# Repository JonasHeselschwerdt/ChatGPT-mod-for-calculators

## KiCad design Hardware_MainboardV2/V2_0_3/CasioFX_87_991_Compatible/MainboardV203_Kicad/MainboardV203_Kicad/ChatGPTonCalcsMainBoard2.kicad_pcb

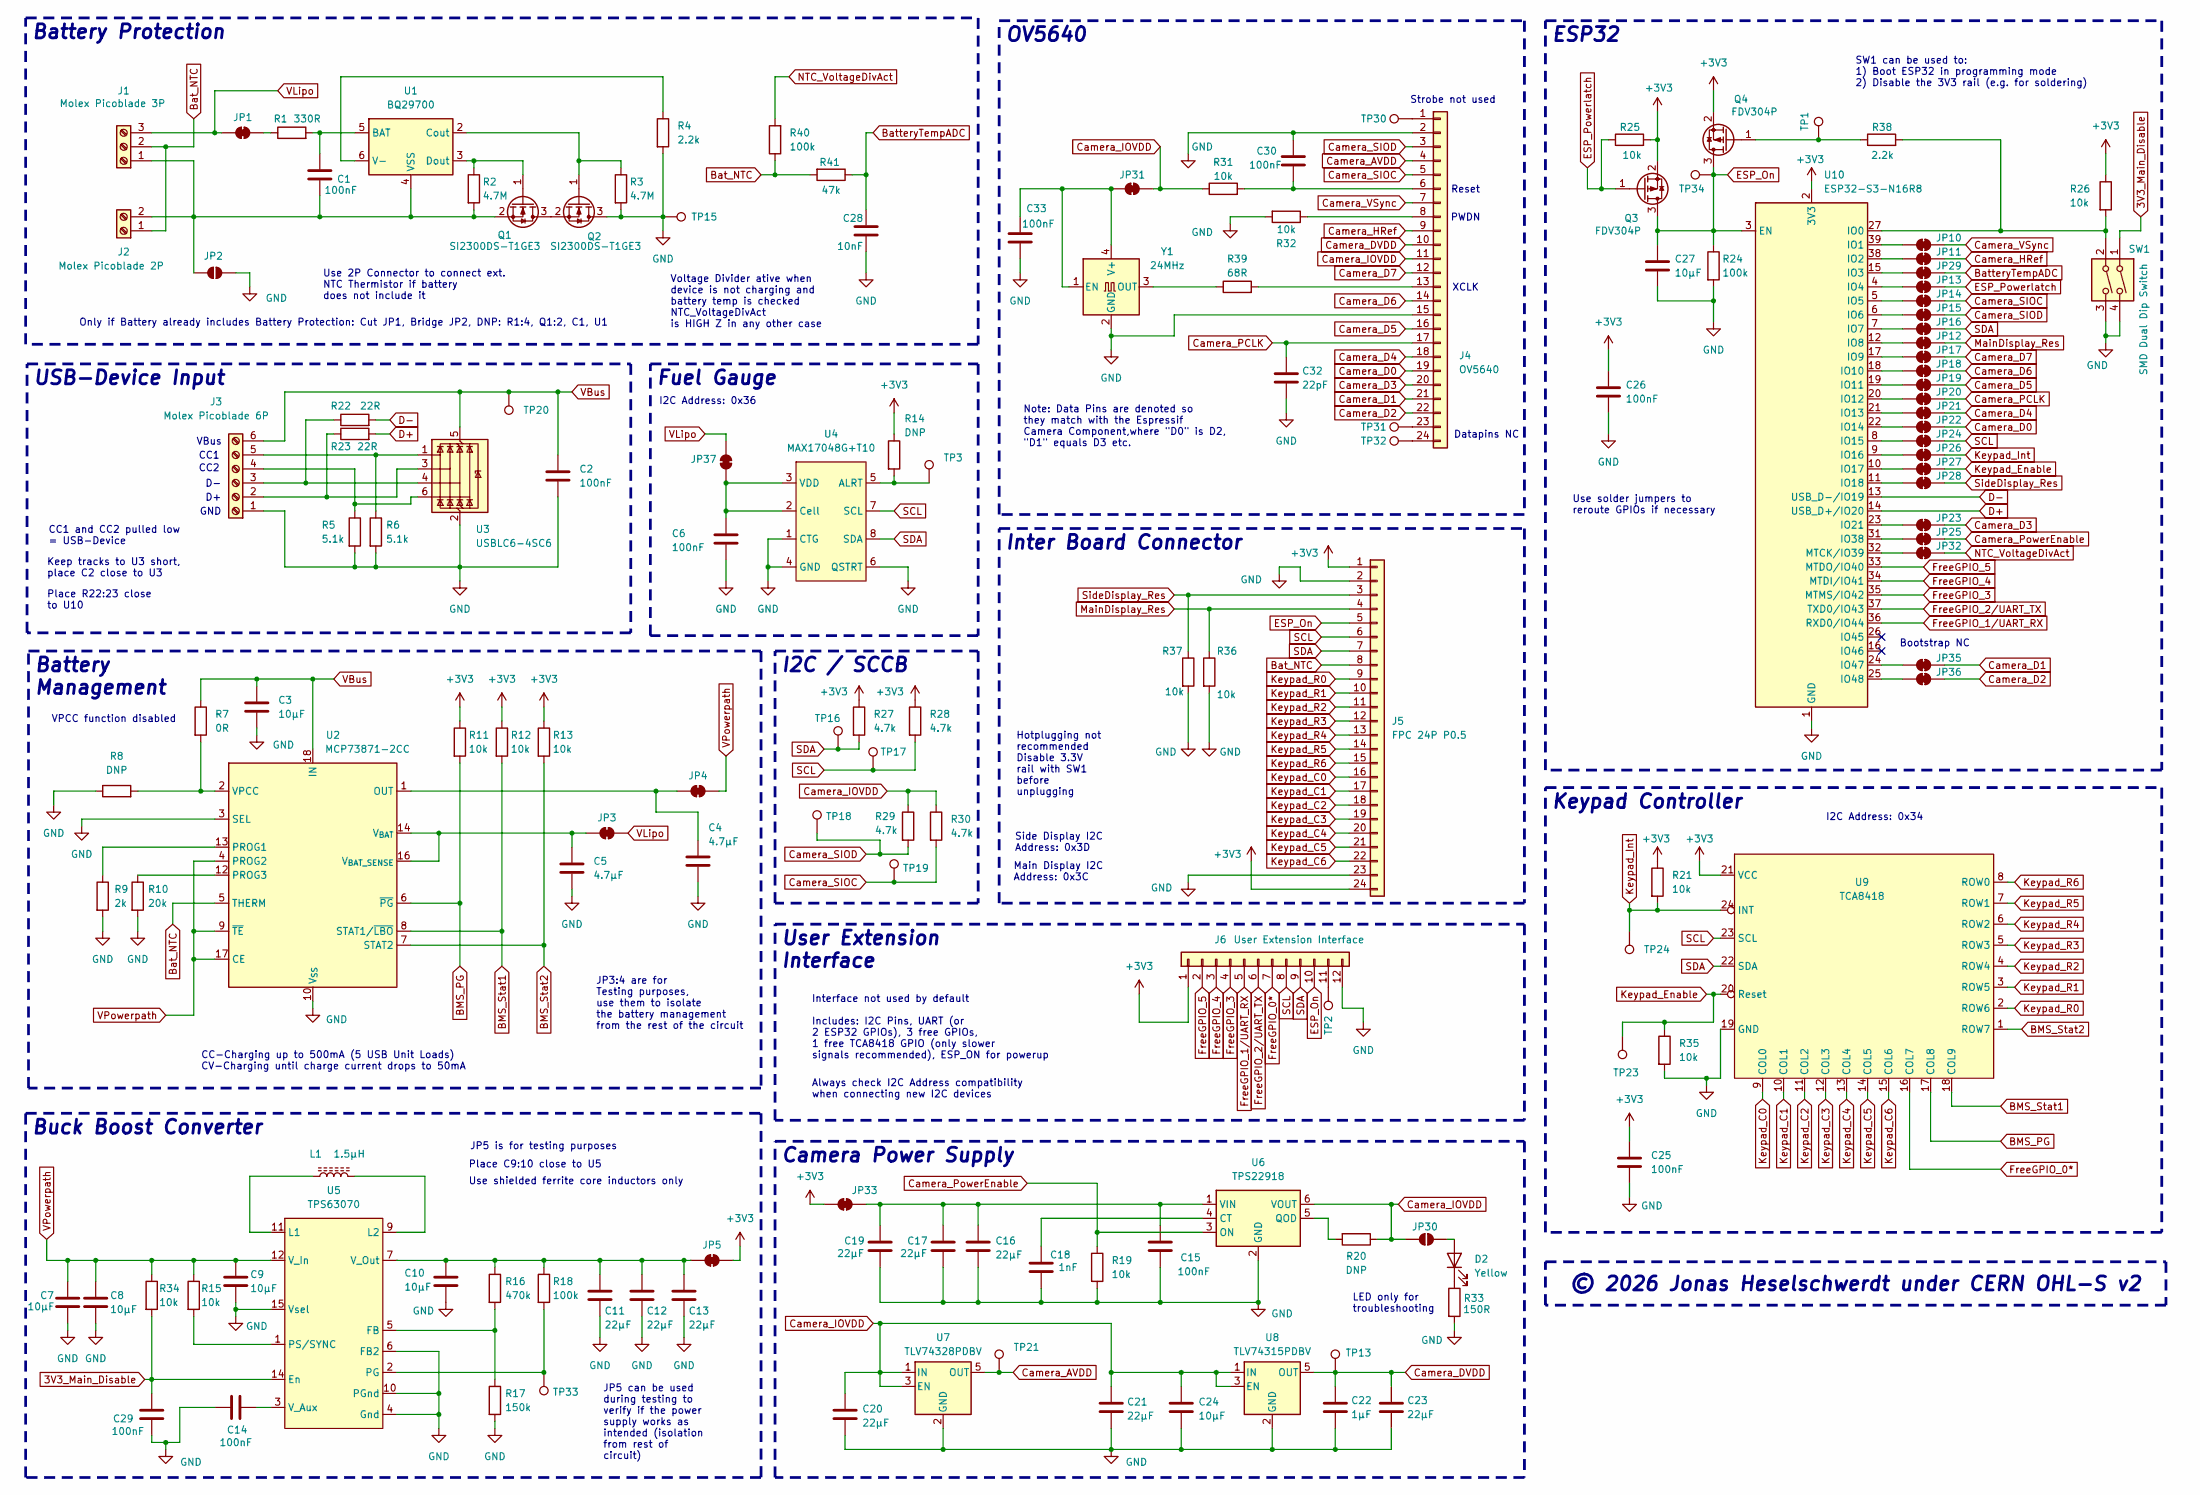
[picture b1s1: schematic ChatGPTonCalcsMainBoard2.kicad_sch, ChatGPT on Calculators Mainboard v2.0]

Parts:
C1, C2, C6, C14, C15, C25, C26, C29, C30, C33: 100nF; C_0603_1608Metric
C3, C7, C8, C9, C10, C24, C27: 10µF; C_0603_1608Metric
C4, C5: 4.7µF; C_0603_1608Metric
C11, C12, C13, C16, C17, C19, C20, C21, C23: 22µF; C_0603_1608Metric
C18: 1nF; C_0603_1608Metric
C22: 1µF; C_0603_1608Metric
C28: 10nF; C_0603_1608Metric
C32: 22pF; C_0603_1608Metric
D2: Yellow; LED_0603_1608Metric
J1: Molex Picoblade 3P; Molex_PicoBlade_53261-0371_1x03-1MP_P1.25mm_Horizontal
J2: Molex Picoblade 2P; Molex_PicoBlade_53261-0271_1x02-1MP_P1.25mm_Horizontal
J3: Molex Picoblade 6P; Molex_PicoBlade_53261-0671_1x06-1MP_P1.25mm_Horizontal
J4: OV5640; 24Pin_FPC_P0.5_RecommendedLayout
J5: FPC 24P P0.5; 24Pin_FPC_P0.5_RecommendedLayout
J6: User Extension Interface; Calc_ExtensionInterfaceV202
JP1, JP3, JP4, JP5, JP10, JP11, JP12, JP13, JP14, JP15, JP16, JP17, JP18, JP19, JP20, JP21, JP22, JP23, JP24, JP25, JP26, JP27, JP28, JP29, JP31, JP32, JP33, JP35, JP36, JP37: SolderJumper_2_Bridged; SolderJumper-2_P1.3mm_Bridged_RoundedPad1.0x1.5mm
JP2, JP30: SolderJumper_2_Open; SolderJumper-2_P1.3mm_Open_RoundedPad1.0x1.5mm
L1: 1.5µH; SPM5030VT-1R5M-D
Q1, Q2: SI2300DS-T1GE3; TSOT-23
Q3, Q4: FDV304P; TSOT-23
R1: 330R; R_0603_1608Metric
R2, R3: 4.7M; R_0603_1608Metric
R4, R38: 2.2k; R_0603_1608Metric
R5, R6: 5.1k; R_0603_1608Metric
R7: 0R; R_0603_1608Metric
R8, R14, R20: DNP; R_0603_1608Metric
R9: 2k; R_0603_1608Metric
R10: 20k; R_0603_1608Metric
R11, R12, R13, R15, R19, R21, R25, R26, R31, R32, R34, R35, R36, R37: 10k; R_0603_1608Metric
R16: 470k; R_0603_1608Metric
R17: 150k; R_0603_1608Metric
R18, R24, R40: 100k; R_0603_1608Metric
R22, R23: 22R; R_0603_1608Metric
R27, R28, R29, R30: 4.7k; R_0603_1608Metric
R33: 150R; R_0603_1608Metric
R39: 68R; R_0603_1608Metric
R41: 47k; R_0603_1608Metric
SW1: SMD Dual Dip Switch; 2P_SMD_DHA-02TQR
TP1, TP2, TP3, TP30, TP31, TP32, TP33, TP34: TestPoint; TestPoint_Pad_D1.0mm
TP13, TP15, TP16, TP17, TP18, TP19, TP20, TP21, TP23, TP24: TestPoint_Pad_D1.0mm
U1: BQ29700; WSON-6_1.5x1.5mm_P0.5mm
U2: MCP73871-2CC; QFN-20-1EP_4x4mm_P0.5mm_EP2.5x2.5mm_ThermalVias
U3: USBLC6-4SC6; SOT-23-6
U4: MAX17048G+T10; TDFN-8-1EP_2x2mm_P0.5mm_EP0.8x1.2mm
U5: TPS63070; TPS63070X
U6: TPS22918; SOT-23-6
U7: TLV74328PDBV; SOT-23-5
U8: TLV74315PDBV; SOT-23-5
U9: TCA8418; WQFN-24-1EP_4x4mm_P0.5mm_EP2.45x2.45mm_ThermalVias
U10: ESP32-S3-N16R8; ESP32-S3_Wroom_No_EP
Y1: 24MHz; Oscillator_SMD_EuroQuartz_XO32-4Pin_3.2x2.5mm

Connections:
3V3_Main_Disable: C29.1, R34.2, SW1.1, U5.14 (En)
+3V3: C25.1, C26.1, J5.1, J5.24, J6.1, JP5.2 (B), JP33.1 (A), Q3.2 (S), Q4.2 (S), R11.1, R12.1, R13.1, R14.1, R21.1, R25.2, R26.1, R27.1, R28.1, U9.21 (VCC), U10.2 (3V3)
BMS_PG: R11.2, U2.6 (~PG), U9.17 (COL8)
BMS_Stat1: R12.2, U2.8 (STAT1/~LBO), U9.18 (COL9)
BMS_Stat2: R13.2, U2.7 (STAT2), U9.1 (ROW7)
Bat_NTC: J1.2, J2.1, J5.8, R40.1, R41.2, U2.5 (THERM)
BatteryTempADC: C28.1, JP29.2 (B), R41.1
Camera_AVDD: J4.4, TP21.1 (1_1), U7.5 (OUT)
Camera_D0: J4.19, JP22.2 (B)
Camera_D1: J4.21, JP35.2 (B)
Camera_D2: J4.22, JP36.2 (B)
Camera_D3: J4.20, JP23.2 (B)
Camera_D4: J4.18, JP21.2 (B)
Camera_D5: J4.16, JP19.2 (B)
Camera_D6: J4.14, JP18.2 (B)
Camera_D7: J4.12, JP17.2 (B)
Camera_DVDD: C22.1, C23.1, J4.10, TP13.1 (1_1), U8.5 (OUT)
Camera_HRef: J4.9, JP11.2 (B)
Camera_IOVDD: C20.1, C21.1, C24.1, J4.11, JP30.1 (A), JP31.2 (B), R20.1, R29.1, R30.1, R31.1, U6.6 (VOUT), U7.1 (IN), U7.3 (EN), U8.1 (IN), U8.3 (EN)
Camera_PCLK: C32.1, J4.17, JP20.2 (B)
Camera_PowerEnable: JP25.2 (B), R19.1, U6.3 (ON)
Camera_SIOC: J4.5, JP14.2 (B), R30.2, TP19.1 (1_1)
Camera_SIOD: J4.3, JP15.2 (B), R29.2, TP18.1 (1_1)
Camera_VSync: J4.7, JP10.2 (B)
D+: R23.2, U10.14 (USB_D+/IO20)
D-: R22.2, U10.13 (USB_D-/IO19)
ESP_On: C27.1, J5.5, J6.10, Q3.3 (D), Q4.3 (D), R24.1, TP34.1 (1_1), U10.3 (EN)
ESP_Powerlatch: JP13.2 (B), Q3.1 (G), R25.1
FreeGPIO_0*: J6.7, U9.16 (COL7)
FreeGPIO_1/UART_RX: J6.5, U10.36 (RXD0/IO44)
FreeGPIO_2/UART_TX: J6.6, U10.37 (TXD0/IO43)
FreeGPIO_3: J6.4, U10.35 (MTMS/IO42)
FreeGPIO_4: J6.3, U10.34 (MTDI/IO41)
FreeGPIO_5: J6.2, U10.33 (MTDO/IO40)
GND: C2.2, C3.2, C4.2, C5.2, C6.2, C7.2, C8.2, C9.2, C10.2, C11.2, C12.2, C13.2, C14.1, C15.2, C16.2, C17.2, C18.2, C19.2, C20.2, C21.2, C22.2, C23.2, C24.2, C25.2, C26.2, C27.2, C28.2, C29.2, C30.2, C32.2, C33.2, J3.1, J4.2, J4.15, J5.2, J5.23, J6.12, JP2.2 (B), Q2.3 (D), R3.2, R4.2, R5.2, R6.2, R8.1, R9.2, R10.2, R17.2, R19.2, R24.2, R32.2, R33.2, R35.2, R36.2, R37.2, SW1.3, SW1.4, TP15.1 (1_1), U2.3 (SEL), U2.10 (V_{SS}), U2.11 (V_{SS}), U2.21 (V_{SS}), U3.2 (GND), U4.1 (CTG), U4.4 (GND), U4.6 (QSTRT), U4.9 (EP), U5.4 (Gnd), U5.6 (FB2), U5.10 (PGnd), U5.15 (Vsel), U6.2 (GND), U7.2 (GND), U8.2 (GND), U9.19 (GND), U10.1 (GND), U10.40 (GND), U10.41 (GND), Y1.2 (GND)
Keypad_C0: J5.16, U9.9 (COL0)
Keypad_C1: J5.17, U9.10 (COL1)
Keypad_C2: J5.18, U9.11 (COL2)
Keypad_C3: J5.19, U9.12 (COL3)
Keypad_C4: J5.20, U9.13 (COL4)
Keypad_C5: J5.21, U9.14 (COL5)
Keypad_C6: J5.22, U9.15 (COL6)
Keypad_Enable: JP27.2 (B), R35.1, TP23.1 (1_1), U9.20 (Reset)
Keypad_Int: JP26.2 (B), R21.2, TP24.1 (1_1), U9.24 (INT)
Keypad_R0: J5.9, U9.2 (ROW6)
Keypad_R1: J5.10, U9.3 (ROW5)
Keypad_R2: J5.11, U9.4 (ROW4)
Keypad_R3: J5.12, U9.5 (ROW3)
Keypad_R4: J5.13, U9.6 (ROW2)
Keypad_R5: J5.14, U9.7 (ROW1)
Keypad_R6: J5.15, U9.8 (ROW0)
MainDisplay_Res: J5.4, JP12.2 (B), R36.1
NTC_VoltageDivAct: JP32.2 (B), R40.2
unnamed: D2.2 (A), JP30.2 (B)
unnamed: D2.1 (K), R33.1
unnamed: C1.2, J1.1, J2.2, JP2.1 (A), Q1.2 (S), R2.2, U1.4 (VSS)
unnamed: J3.2, R23.1, U3.3 (I/O2)
unnamed: J3.3, R22.1, U3.4 (I/O3)
unnamed: J3.4, R5.1, U3.6 (I/O4)
unnamed: J3.5, R6.1, U3.1 (I/O1)
unnamed: J4.1, TP30.1 (1_1)
unnamed: C30.1, J4.6, R31.2
unnamed: J4.8, R32.1
unnamed: J4.13, R39.2
unnamed: J4.23, TP31.1 (1_1)
unnamed: J4.24, TP32.1 (1_1)
unnamed: J6.11, TP2.1 (1_1)
unnamed: JP1.2 (B), R1.1
unnamed: C5.1, JP3.1 (A), U2.14 (V_{BAT}), U2.15 (V_{BAT}), U2.16 (V_{BAT_SENSE})
unnamed: C4.1, JP4.1 (A), U2.1 (OUT), U2.20 (OUT)
unnamed: C10.1, C11.1, C12.1, C13.1, JP5.1 (A), R16.1, R18.1, U5.7 (V_Out)
unnamed: JP10.1 (A), U10.39 (IO1)
unnamed: JP11.1 (A), U10.38 (IO2)
unnamed: JP12.1 (A), U10.12 (IO8)
unnamed: JP13.1 (A), U10.4 (IO4)
unnamed: JP14.1 (A), U10.5 (IO5)
unnamed: JP15.1 (A), U10.6 (IO6)
unnamed: JP16.1 (A), U10.7 (IO7)
unnamed: JP17.1 (A), U10.17 (IO9)
unnamed: JP18.1 (A), U10.18 (IO10)
unnamed: JP19.1 (A), U10.19 (IO11)
unnamed: JP20.1 (A), U10.20 (IO12)
unnamed: JP21.1 (A), U10.21 (IO13)
unnamed: JP22.1 (A), U10.22 (IO14)
unnamed: JP23.1 (A), U10.23 (IO21)
unnamed: JP24.1 (A), U10.8 (IO15)
unnamed: JP25.1 (A), U10.31 (IO38)
unnamed: JP26.1 (A), U10.9 (IO16)
unnamed: JP27.1 (A), U10.10 (IO17)
unnamed: JP28.1 (A), U10.11 (IO18)
unnamed: JP29.1 (A), U10.15 (IO3)
unnamed: C33.1, JP31.1 (A), Y1.1 (EN), Y1.4 (V+)
unnamed: JP32.1 (A), U10.32 (MTCK/IO39)
unnamed: C15.1, C16.1, C17.1, C19.1, JP33.2 (B), U6.1 (VIN)
unnamed: JP35.1 (A), U10.24 (IO47)
unnamed: JP36.1 (A), U10.25 (IO48)
unnamed: C6.1, JP37.1 (A), U4.2 (Cell), U4.3 (VDD)
unnamed: Q1.3 (D), Q2.2 (S)
unnamed: Q1.1 (G), R2.1, U1.3 (Dout)
unnamed: Q2.1 (G), R3.1, U1.2 (Cout)
unnamed: Q4.1 (G), R38.1, TP1.1 (1_1)
unnamed: C1.1, R1.2, U1.5 (BAT)
unnamed: R4.1, U1.6 (V-)
unnamed: R9.1, U2.13 (PROG1)
unnamed: R10.1, U2.12 (PROG3)
unnamed: R7.2, R8.2, U2.2 (VPCC)
unnamed: R14.2, TP3.1 (1_1), U4.5 (ALRT)
unnamed: R16.2, R17.1, U5.5 (FB)
unnamed: L1.1, U5.11 (L1)
unnamed: L1.2, U5.9 (L2)
unnamed: R18.2, TP33.1 (1_1), U5.2 (PG)
unnamed: R15.2, U5.1 (PS/SYNC)
unnamed: C14.2, U5.3 (V_Aux)
unnamed: C18.1, U6.4 (CT)
unnamed: R20.2, U6.5 (QOD)
unnamed: R26.2, R38.2, SW1.2, U10.27 (IO0)
unnamed: R39.1, Y1.3 (OUT)
SCL: J5.6, J6.8, JP24.2 (B), R28.2, TP17.1 (1_1), U4.7 (SCL), U9.23 (SCL)
SDA: J5.7, J6.9, JP16.2 (B), R27.2, TP16.1 (1_1), U4.8 (SDA), U9.22 (SDA)
SideDisplay_Res: J5.3, JP28.2 (B), R37.1
VBus: C2.1, C3.1, J3.6, R7.1, TP20.1 (1_1), U2.18 (IN), U2.19 (IN), U3.5 (VBUS)
VLipo: J1.3, JP1.1 (A), JP3.2 (B), JP37.2 (B)
VPowerpath: C7.1, C8.1, C9.1, JP4.2 (B), R15.1, R34.1, U2.4 (PROG2), U2.9 (~TE), U2.17 (CE), U5.12 (V_In)

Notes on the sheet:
CC1 and CC2 pulled low = USB-Device
Side Display I2C Address: 0x3D
JP5 can be used during testing to verify if the power supply works as intended (isolation from rest of circuit)
Bootstrap NC
Use 2P Connector to connect ext. NTC Thermistor if battery does not include it
VPCC function disabled
XCLK
Strobe not used
Interface not used by default Includes: I2C Pins, UART (or 2 ESP32 GPIOs), 3 free GPIOs, 1 free TCA8418 GPIO (only slower signals recommended), ESP_ON for powerup
JP5 is for testing purposes
Always check I2C Address compatibility when connecting new I2C devices
CC1
Main Display I2C Address: 0x3C
PWDN
Hotplugging not recommended Disable 3.3V rail with SW1 before unplugging
I2C Address: 0x36
Only if Battery already includes Battery Protection: Cut JP1, Bridge JP2, DNP: R1:4, Q1:2, C1, U1
CC-Charging up to 500mA (5 USB Unit Loads) CV-Charging until charge current drops to 50mA
Place C9:10 close to U5
CC2
Datapins NC
GND
JP3:4 are for Testing purposes, use them to isolate the battery management from the rest of the circuit
VBus
I2C Address: 0x34
Reset
LED only for troubleshooting
Voltage Divider ative when device is not charging and battery temp is checked NTC_VoltageDivAct is HIGH Z in any other case
Note: Data Pins are denoted so they match with the Espressif Camera Component,where "D0" is D2, "D1" equals D3 etc.
Keep tracks to U3 short, place C2 close to U3
Use shielded ferrite core inductors only
Use solder jumpers to reroute GPIOs if necessary
SW1 can be used to: 1) Boot ESP32 in programming mode 2) Disable the 3V3 rail (e.g. for soldering)
Place R22:23 close to U10
Keypad Controller
OV5640
Battery Protection
Buck Boost Converter
Inter Board Connector
I2C / SCCB

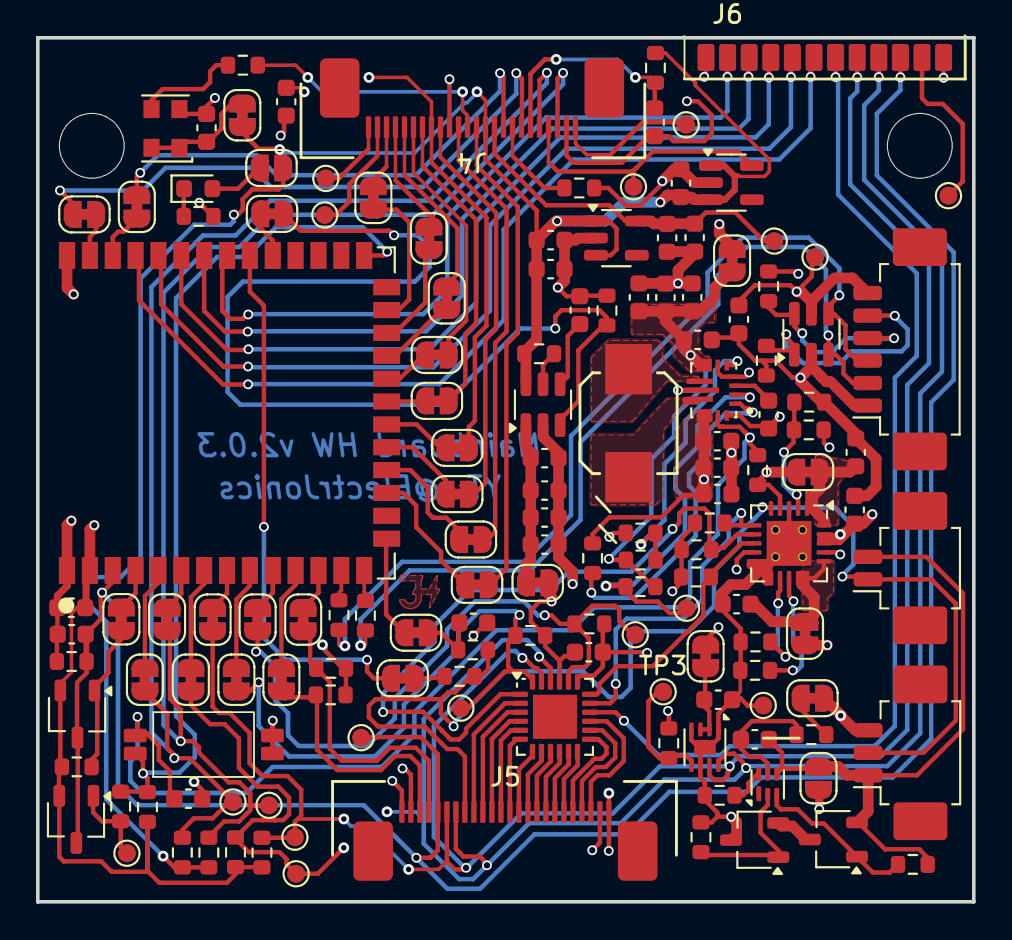
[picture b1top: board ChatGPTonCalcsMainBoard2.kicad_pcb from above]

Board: 4 copper layers, 52.0 x 48.0 mm, 147 parts (0 on the bottom side), 123 nets.

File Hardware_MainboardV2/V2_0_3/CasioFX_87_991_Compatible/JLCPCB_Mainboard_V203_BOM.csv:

Designator,Comment,Footprint,JLCPCB Part #
"C1,C2,C6,C14,C15,C25,C26,C29,C30,C33",100nF,Capacitor_SMD:C_0603_1608Metric,C45000
"C3,C7,C8,C9,C10,C24,C27",10uF,Capacitor_SMD:C_0603_1608Metric,C92487
"C4,C5",4.7uF,Capacitor_SMD:C_0603_1608Metric,C909850
"C11,C12,C13,C16,C17,C19,C20,C21,C23",22uF,Capacitor_SMD:C_0603_1608Metric,C22367828
C18,1nF,Capacitor_SMD:C_0603_1608Metric,C1588
C22,1uF,Capacitor_SMD:C_0603_1608Metric,C597124
C28,10nF,Capacitor_SMD:C_0603_1608Metric,C1589
C32,22pF,Capacitor_SMD:C_0603_1608Metric,C2169813
D2,Yellow,LED_SMD:LED_0603_1608Metric,C5160703
J1,Molex Picoblade 3P,Connector_Molex:Molex_PicoBlade_53261-0371_1x03-1MP_P1.25mm_Horizontal,C293630
J3,Molex Picoblade 6P,Connector_Molex:Molex_PicoBlade_53261-0671_1x06-1MP_P1.25mm_Horizontal,C17393620
J4,OV5640,ChatGPTonCalcsFootprints:24Pin_FPC_P0.5_RecommendedLayout,C262643
J5,FPC 24P P0.5,ChatGPTonCalcsFootprints:24Pin_FPC_P0.5_RecommendedLayout,C262643
L1,1.5uH,ChatGPTonCalcsFootprints:SPM5030VT-1R5M-D,C542312
"Q1,Q2",SI2300DS-T1GE3,Package_TO_SOT_SMD:TSOT-23,C72271
"Q3,Q4",FDV304P,Package_TO_SOT_SMD:TSOT-23,C10884
R1,330R,Resistor_SMD:R_0603_1608Metric,C23138
"R2,R3",4.7M,Resistor_SMD:R_0603_1608Metric,C23163
"R4,R38",2.2k,Resistor_SMD:R_0603_1608Metric,C4190
"R5,R6",5.1k,Resistor_SMD:R_0603_1608Metric,C23186
R7,0R,Resistor_SMD:R_0603_1608Metric,C21189
R9,2k,Resistor_SMD:R_0603_1608Metric,C22975
R10,20k,Resistor_SMD:R_0603_1608Metric,C4184
"R11,R12,R13,R15,R19,R21,R25,R26,R31,R32,R34,R35,R36,R37",10k,Resistor_SMD:R_0603_1608Metric,C25804
R16,470k,Resistor_SMD:R_0603_1608Metric,C23178
R17,150k,Resistor_SMD:R_0603_1608Metric,C22807
"R18,R24,R40",100k,Resistor_SMD:R_0603_1608Metric,C25803
"R22,R23",22R,Resistor_SMD:R_0603_1608Metric,C23345
"R27,R28,R29,R30",4.7k,Resistor_SMD:R_0603_1608Metric,C23162
R33,150R,Resistor_SMD:R_0603_1608Metric,C22808
R39,68R,Resistor_SMD:R_0603_1608Metric,C27592
R41,47k,Resistor_SMD:R_0603_1608Metric,C25819
SW1,SMD Dual Dip Switch,ChatGPTonCalcsFootprints:2P_SMD_DHA-02TQR,C224990
U1,BQ29700,Package_SON:WSON-6_1.5x1.5mm_P0.5mm,C183096
U2,MCP73871-2CC,Package_DFN_QFN:QFN-20-1EP_4x4mm_P0.5mm_EP2.5x2.5mm_ThermalVias,C5121473
U3,USBLC6-4SC6,Package_TO_SOT_SMD:SOT-23-6,C111212
U4,MAX17048G+T10,Package_DFN_QFN:TDFN-8-1EP_2x2mm_P0.5mm_EP0.8x1.2mm,C2682616
U5,TPS63070,ChatGPTonCalcsFootprints:TPS63070X,C2071354
U6,TPS22918,Package_TO_SOT_SMD:SOT-23-6,C131941
U7,TLV74328PDBV,Package_TO_SOT_SMD:SOT-23-5,C408971
U8,TLV74315PDBV,Package_TO_SOT_SMD:SOT-23-5,C2867152
U9,TCA8418,Package_DFN_QFN:WQFN-24-1EP_4x4mm_P0.5mm_EP2.45x2.45mm_ThermalVias,C138713
U10,ESP32-S3-N16R8,ChatGPTonCalcsFootprints:ESP32-S3_Wroom_No_EP,C2913202
Y1,24MHz,Oscillator:Oscillator_SMD_EuroQuartz_XO32-4Pin_3.2x2.5mm,C160455

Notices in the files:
Hardware_MainboardV2/V2_0_3/CasioFX_87_991_Compatible/MainboardV203_Kicad/MainboardV203_Kicad/ChatGPTonCalcsMainBoard2.kicad_pcb:
© 2026 Jonas Heselschwerdt under CERN OHL-S v2
